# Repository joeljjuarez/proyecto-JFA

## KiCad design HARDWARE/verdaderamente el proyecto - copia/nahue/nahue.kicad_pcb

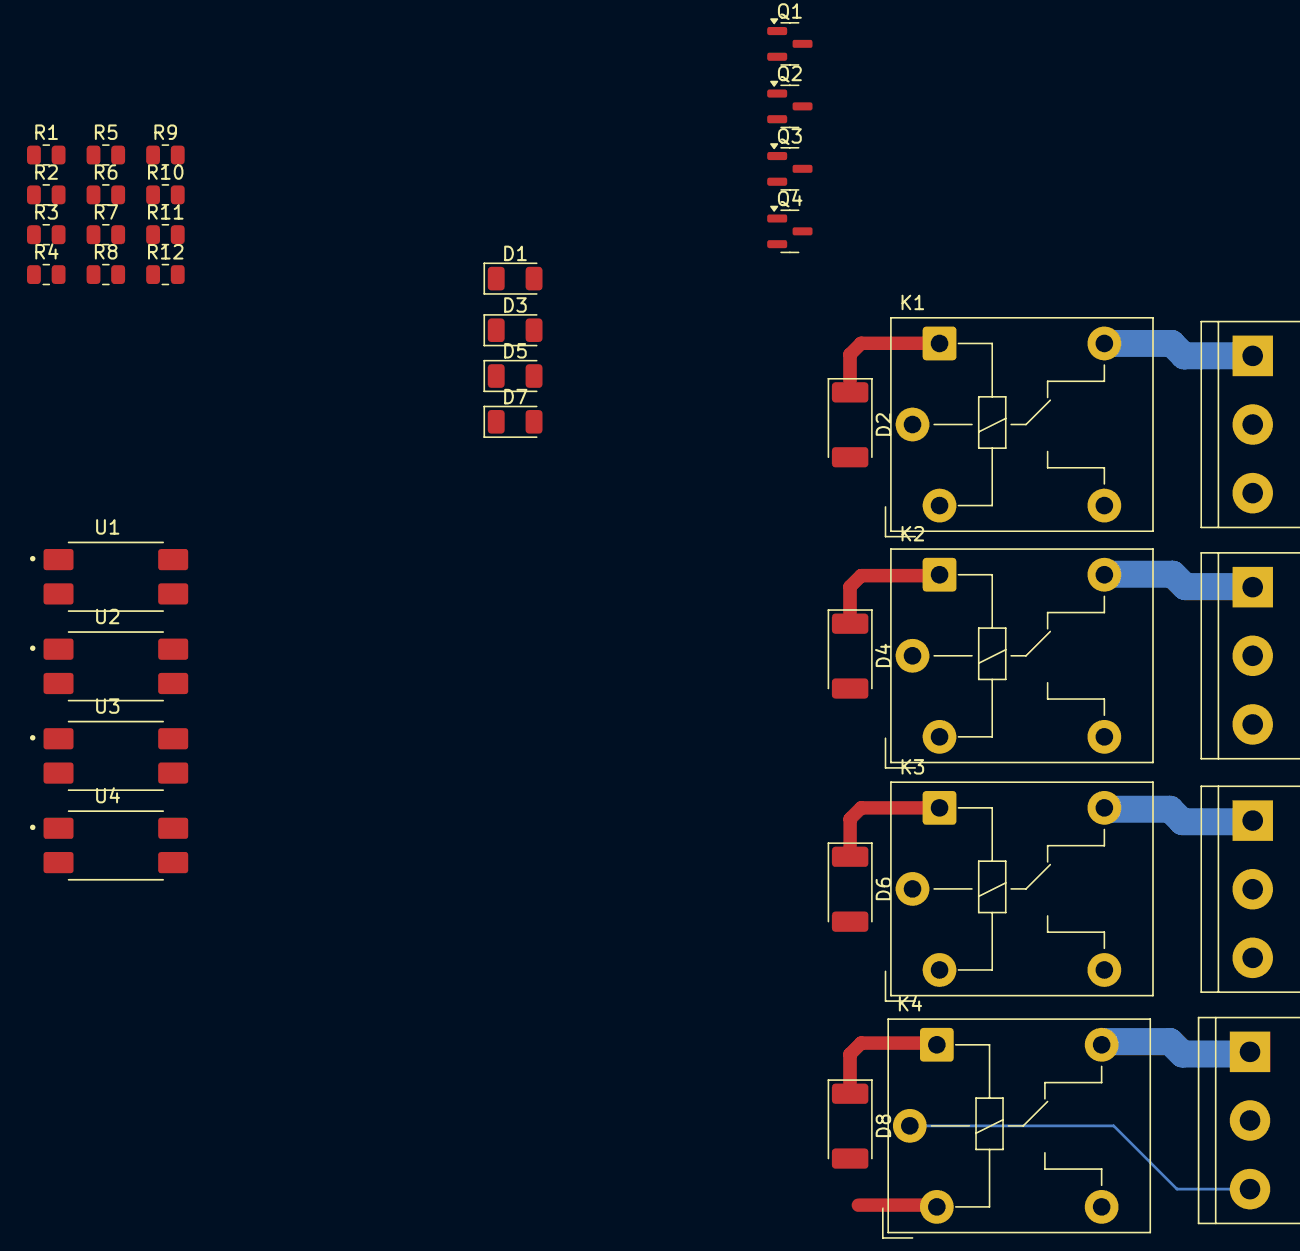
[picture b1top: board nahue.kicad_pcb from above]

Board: 2 copper layers, 36 parts (0 on the bottom side), 31 nets.

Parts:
D1, D3, D5, D7: led smd 1206; LED_1206_3216Metric
D2, D4, D6, D8: SM4007; D_MELF
J3, J4, J5, J6: Conn_02x03_Odd_Even; TerminalBlock_bornier-3_P5.08mm
K1, K2, K3, K4: JQC-3FF-005-1Z; Relay_SPDT_Hongfa_JQC-3FF_0XX-1Z
Q1, Q2, Q3, Q4: BC847; SOT-23
R1, R4, R7, R10: 220k; R_0805_2012Metric
R2, R5, R8, R11: 1k; R_0805_2012Metric
R3, R6, R9, R12: 220; R_0805_2012Metric
U1, U2, U3, U4: PC817; SOIC254P1000X400-4N

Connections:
+5V: D1.2 (A), D2.1 (K), D3.2 (A), D4.1 (K), D5.2 (A), D6.1 (K), D7.2 (A), D8.1 (K), K1.A1, K2.A1, K3.A1, K4.A1, U1.4, U2.4, U3.4, U4.4
GND: Q1.2 (E), Q2.2 (E), Q3.2 (E), Q4.2 (E), U1.2, U2.2, U3.2, U4.2
INPUT3: R1.1, R7.2
unnamed: D1.1 (K), R3.1
unnamed: D2.2 (A), K1.A2, Q1.3 (C), R3.2
unnamed: D3.1 (K), R6.1
unnamed: D4.2 (A), K2.A2, Q2.3 (C), R6.2
unnamed: D5.1 (K), R9.1
unnamed: D6.2 (A), K3.A2, Q3.3 (C), R9.2
unnamed: D7.1 (K), R12.1
unnamed: D8.2 (A), K4.A2, Q4.3 (C), R12.2
unnamed: J3.1, K1.12
unnamed: J3.3, K1.11
unnamed: J4.1, K2.12
unnamed: J4.3, K2.11
unnamed: J5.1, K4.12
unnamed: J5.3, K4.11
unnamed: J6.1, K3.12
unnamed: J6.3, K3.11
unnamed: Q1.1 (B), R2.2
unnamed: Q2.1 (B), R5.2
unnamed: Q3.1 (B), R8.2
unnamed: Q4.1 (B), R11.2
unnamed: R1.2, U3.1
unnamed: R2.1, U3.3
unnamed: R4.1, U4.1
unnamed: R5.1, U4.3
unnamed: R7.1, U2.1
unnamed: R8.1, U2.3
unnamed: R10.2, U1.1
unnamed: R11.1, U1.3

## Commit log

2025-05-14 agregamos HARDWARE
2025-05-14 SOFTWARE
2025-05-14 agregamos 3D
2025-06-01 actualizacion del kicad
2025-06-01 Actualizar carpeta HARDWARE a proyecto-kicad y eliminar proyecto-JFA
2025-06-02 actualizacion de kicad
2025-06-02 modificacion del kicad
2025-06-02 modificacion de capacitores pararlelo
2025-06-14 se agrego huella del ESP32(falta terminar)
2025-06-18 últimos arreglos 1
2025-06-20 retoques del kicad
2025-06-23 finalizando
2025-06-24 finalizado 2
2025-07-08 duplicacion de placa
2025-07-08 duplicacion
2025-07-14 imprimir placa
2025-11-03 agregamos el codigo
